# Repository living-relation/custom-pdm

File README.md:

# custom-pdm

Personal 12 V power distribution module (PDM) for car accessories: 24 outputs (16 x 7.5 A, 4 x 15 A, 4 x about 31 A on copper offset risers through the lid; one 7.5 A output, A2 OUT2, powers the internal fans, so 23 are for the car) and 24 on/off + 3 analog inputs over three boards, controlled over CAN by a Link G4X ECU.

Based on [corygrant/dingoPDM](https://github.com/corygrant/dingoPDM) (MIT). Personal project, not for sale.

Firmware: which file goes on which board, how to flash it over USB-C, how to check the version and when to update: [docs/firmware-flashing.md](docs/firmware-flashing.md).

Progress and open items: live state lives in this repo ([STATE.md](STATE.md), [BACKLOG.md](BACKLOG.md), `archives/`; see the role table in [AGENTS.md](AGENTS.md)).

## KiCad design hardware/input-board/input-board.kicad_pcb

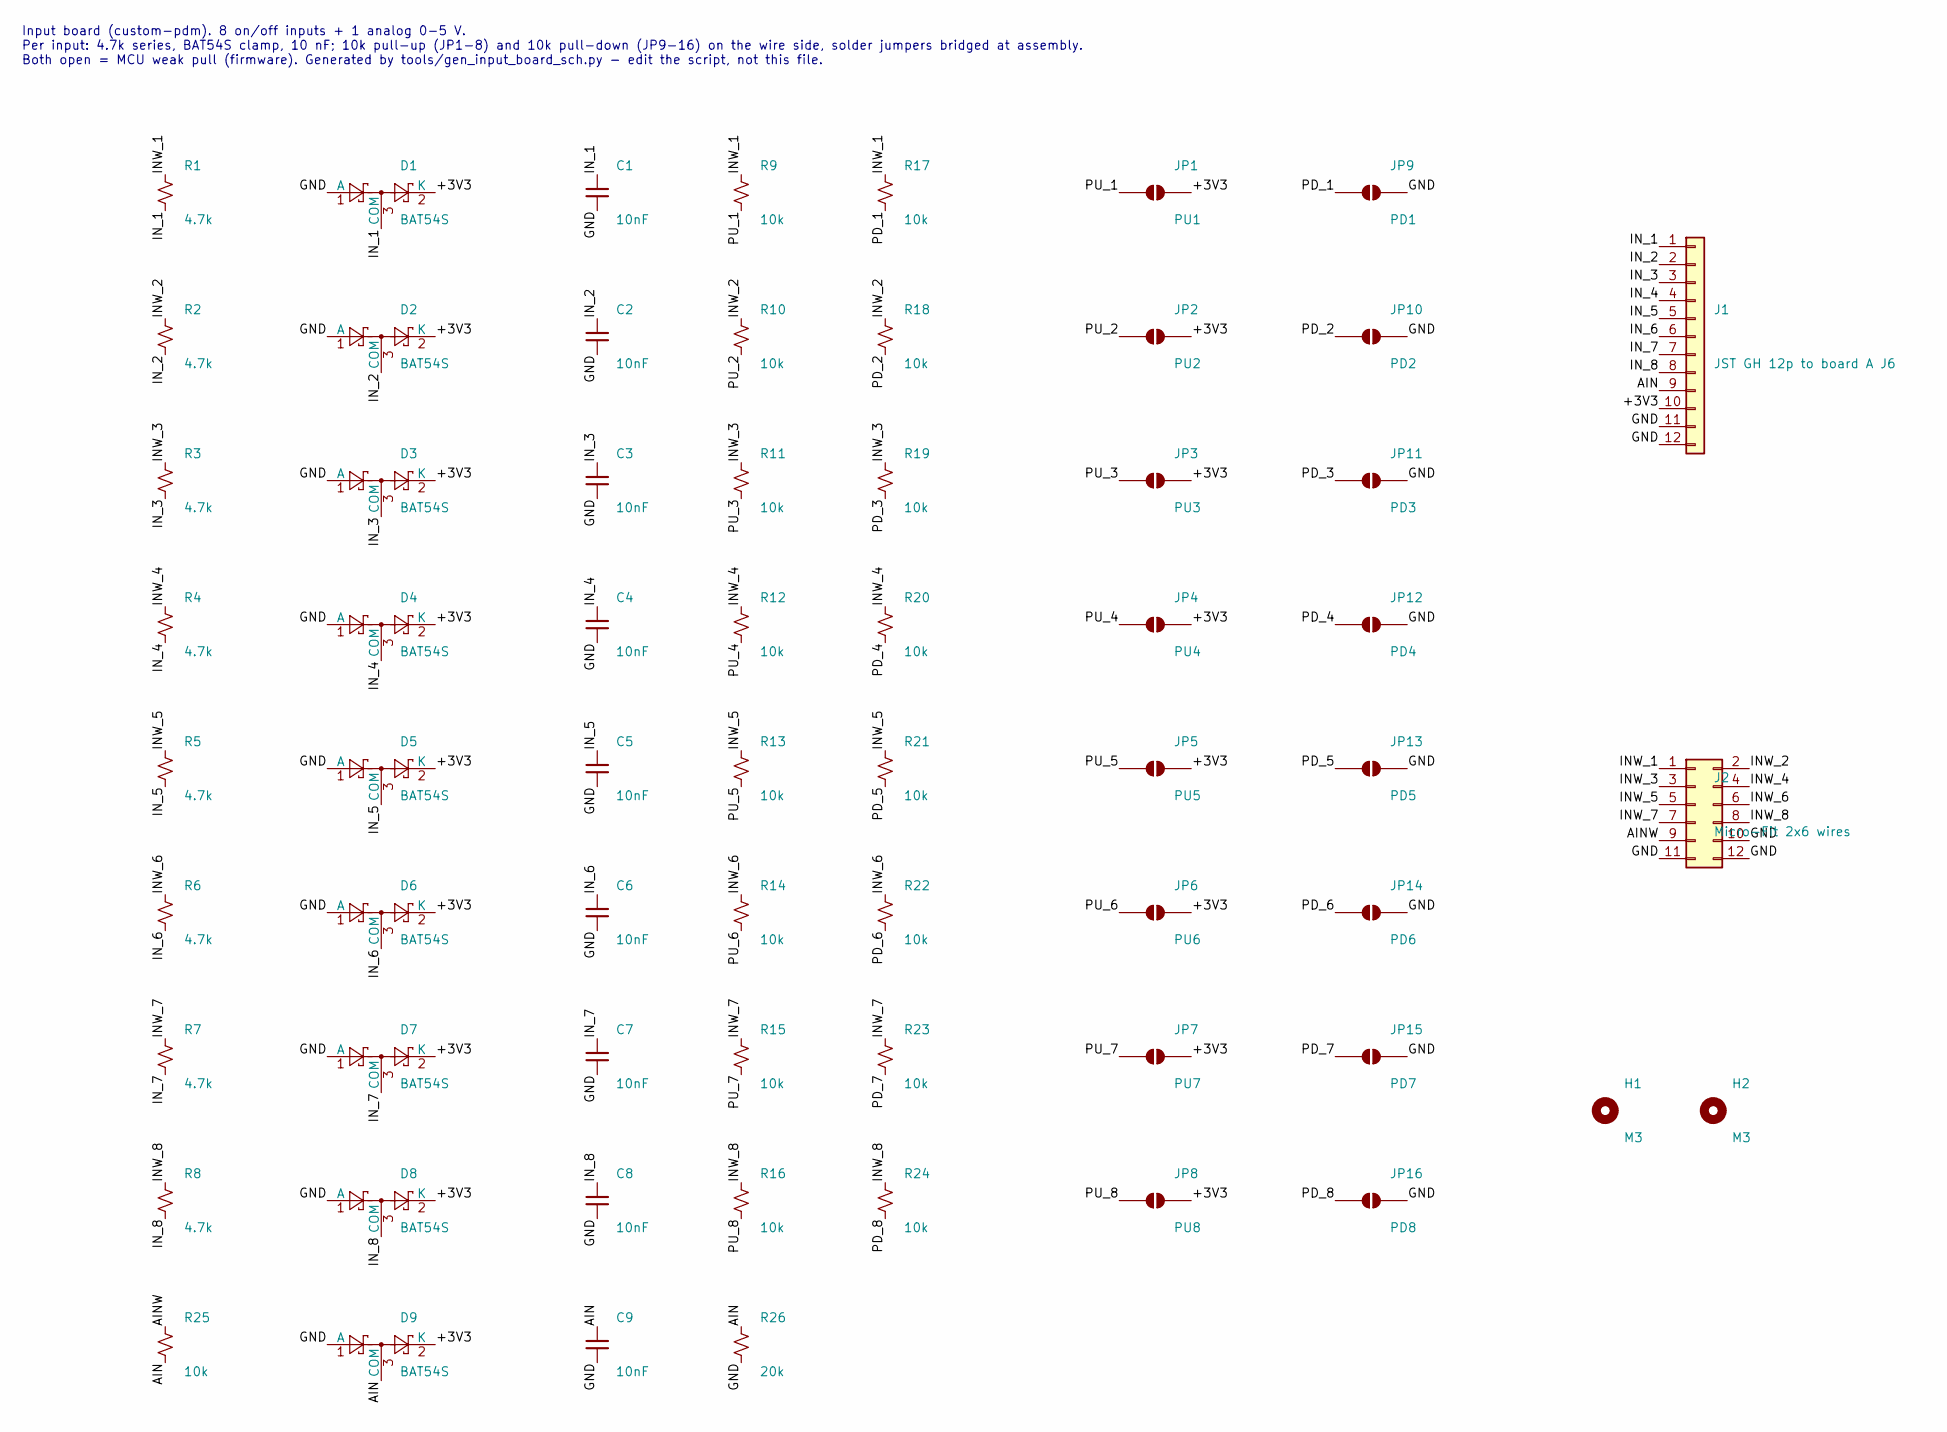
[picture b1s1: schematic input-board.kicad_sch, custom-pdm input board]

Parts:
C1, C2, C3, C4, C5, C6, C7, C8, C9: 10nF; C_0603_1608Metric; MPN 0603B103K500NT; LCSC C57112
D1, D2, D3, D4, D5, D6, D7, D8, D9: BAT54S; SOT-23; MPN BAT54S,215; LCSC C47546
H1, H2: M3; MountingHole_3.2mm_M3
J1: JST GH 12p to board A J6; JST_GH_SM12B-GHS-TB_1x12-1MP_P1.25mm_Horizontal; MPN SM12B-GHS-TB(LF)(SN); LCSC C265421
J2: Micro-Fit 2x6 wires; Molex_Micro-Fit_3.0_43045-1200_2x06_P3.00mm_Horizontal; MPN 0430451200; LCSC C277636
JP1: PU1; SolderJumper-2_P1.3mm_Open_RoundedPad1.0x1.5mm
JP2: PU2; SolderJumper-2_P1.3mm_Open_RoundedPad1.0x1.5mm
JP3: PU3; SolderJumper-2_P1.3mm_Open_RoundedPad1.0x1.5mm
JP4: PU4; SolderJumper-2_P1.3mm_Open_RoundedPad1.0x1.5mm
JP5: PU5; SolderJumper-2_P1.3mm_Open_RoundedPad1.0x1.5mm
JP6: PU6; SolderJumper-2_P1.3mm_Open_RoundedPad1.0x1.5mm
JP7: PU7; SolderJumper-2_P1.3mm_Open_RoundedPad1.0x1.5mm
JP8: PU8; SolderJumper-2_P1.3mm_Open_RoundedPad1.0x1.5mm
JP9: PD1; SolderJumper-2_P1.3mm_Open_RoundedPad1.0x1.5mm
JP10: PD2; SolderJumper-2_P1.3mm_Open_RoundedPad1.0x1.5mm
JP11: PD3; SolderJumper-2_P1.3mm_Open_RoundedPad1.0x1.5mm
JP12: PD4; SolderJumper-2_P1.3mm_Open_RoundedPad1.0x1.5mm
JP13: PD5; SolderJumper-2_P1.3mm_Open_RoundedPad1.0x1.5mm
JP14: PD6; SolderJumper-2_P1.3mm_Open_RoundedPad1.0x1.5mm
JP15: PD7; SolderJumper-2_P1.3mm_Open_RoundedPad1.0x1.5mm
JP16: PD8; SolderJumper-2_P1.3mm_Open_RoundedPad1.0x1.5mm
R1, R2, R3, R4, R5, R6, R7, R8: 4.7k; R_0603_1608Metric; MPN 0603WAF4701T5E; LCSC C23162
R9, R10, R11, R12, R13, R14, R15, R16, R17, R18, R19, R20, R21, R22, R23, R24, R25: 10k; R_0603_1608Metric; MPN 0603WAF1002T5E; LCSC C25804
R26: 20k; R_0603_1608Metric; MPN 0603WAF2002T5E; LCSC C4184

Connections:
/+3V3: D1.2 (K), D2.2 (K), D3.2 (K), D4.2 (K), D5.2 (K), D6.2 (K), D7.2 (K), D8.2 (K), D9.2 (K), J1.10, JP1.2 (B), JP2.2 (B), JP3.2 (B), JP4.2 (B), JP5.2 (B), JP6.2 (B), JP7.2 (B), JP8.2 (B)
/AIN: C9.1, D9.3 (COM), J1.9, R25.2, R26.1
/AINW: J2.9, R25.1
/GND: C1.2, C2.2, C3.2, C4.2, C5.2, C6.2, C7.2, C8.2, C9.2, D1.1 (A), D2.1 (A), D3.1 (A), D4.1 (A), D5.1 (A), D6.1 (A), D7.1 (A), D8.1 (A), D9.1 (A), J1.11, J1.12, J2.10, J2.11, J2.12, JP9.2 (B), JP10.2 (B), JP11.2 (B), JP12.2 (B), JP13.2 (B), JP14.2 (B), JP15.2 (B), JP16.2 (B), R26.2
/INW_1: J2.1, R1.1, R9.1, R17.1
/INW_2: J2.2, R2.1, R10.1, R18.1
/INW_3: J2.3, R3.1, R11.1, R19.1
/INW_4: J2.4, R4.1, R12.1, R20.1
/INW_5: J2.5, R5.1, R13.1, R21.1
/INW_6: J2.6, R6.1, R14.1, R22.1
/INW_7: J2.7, R7.1, R15.1, R23.1
/INW_8: J2.8, R8.1, R16.1, R24.1
/IN_1: C1.1, D1.3 (COM), J1.1, R1.2
/IN_2: C2.1, D2.3 (COM), J1.2, R2.2
/IN_3: C3.1, D3.3 (COM), J1.3, R3.2
/IN_4: C4.1, D4.3 (COM), J1.4, R4.2
/IN_5: C5.1, D5.3 (COM), J1.5, R5.2
/IN_6: C6.1, D6.3 (COM), J1.6, R6.2
/IN_7: C7.1, D7.3 (COM), J1.7, R7.2
/IN_8: C8.1, D8.3 (COM), J1.8, R8.2
/PD_1: JP9.1 (A), R17.2
/PD_2: JP10.1 (A), R18.2
/PD_3: JP11.1 (A), R19.2
/PD_4: JP12.1 (A), R20.2
/PD_5: JP13.1 (A), R21.2
/PD_6: JP14.1 (A), R22.2
/PD_7: JP15.1 (A), R23.2
/PD_8: JP16.1 (A), R24.2
/PU_1: JP1.1 (A), R9.2
/PU_2: JP2.1 (A), R10.2
/PU_3: JP3.1 (A), R11.2
/PU_4: JP4.1 (A), R12.2
/PU_5: JP5.1 (A), R13.2
/PU_6: JP6.1 (A), R14.2
/PU_7: JP7.1 (A), R15.2
/PU_8: JP8.1 (A), R16.2

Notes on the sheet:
Input board (custom-pdm). 8 on/off inputs + 1 analog 0-5 V. Per input: 4.7k series, BAT54S clamp, 10 nF; 10k pull-up (JP1-8) and 10k pull-down (JP9-16) on the wire side, solder jumpers bridged at assembly. Both open = MCU weak pull (firmware). Generated by tools/gen_input_board_sch.py - edit the sc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

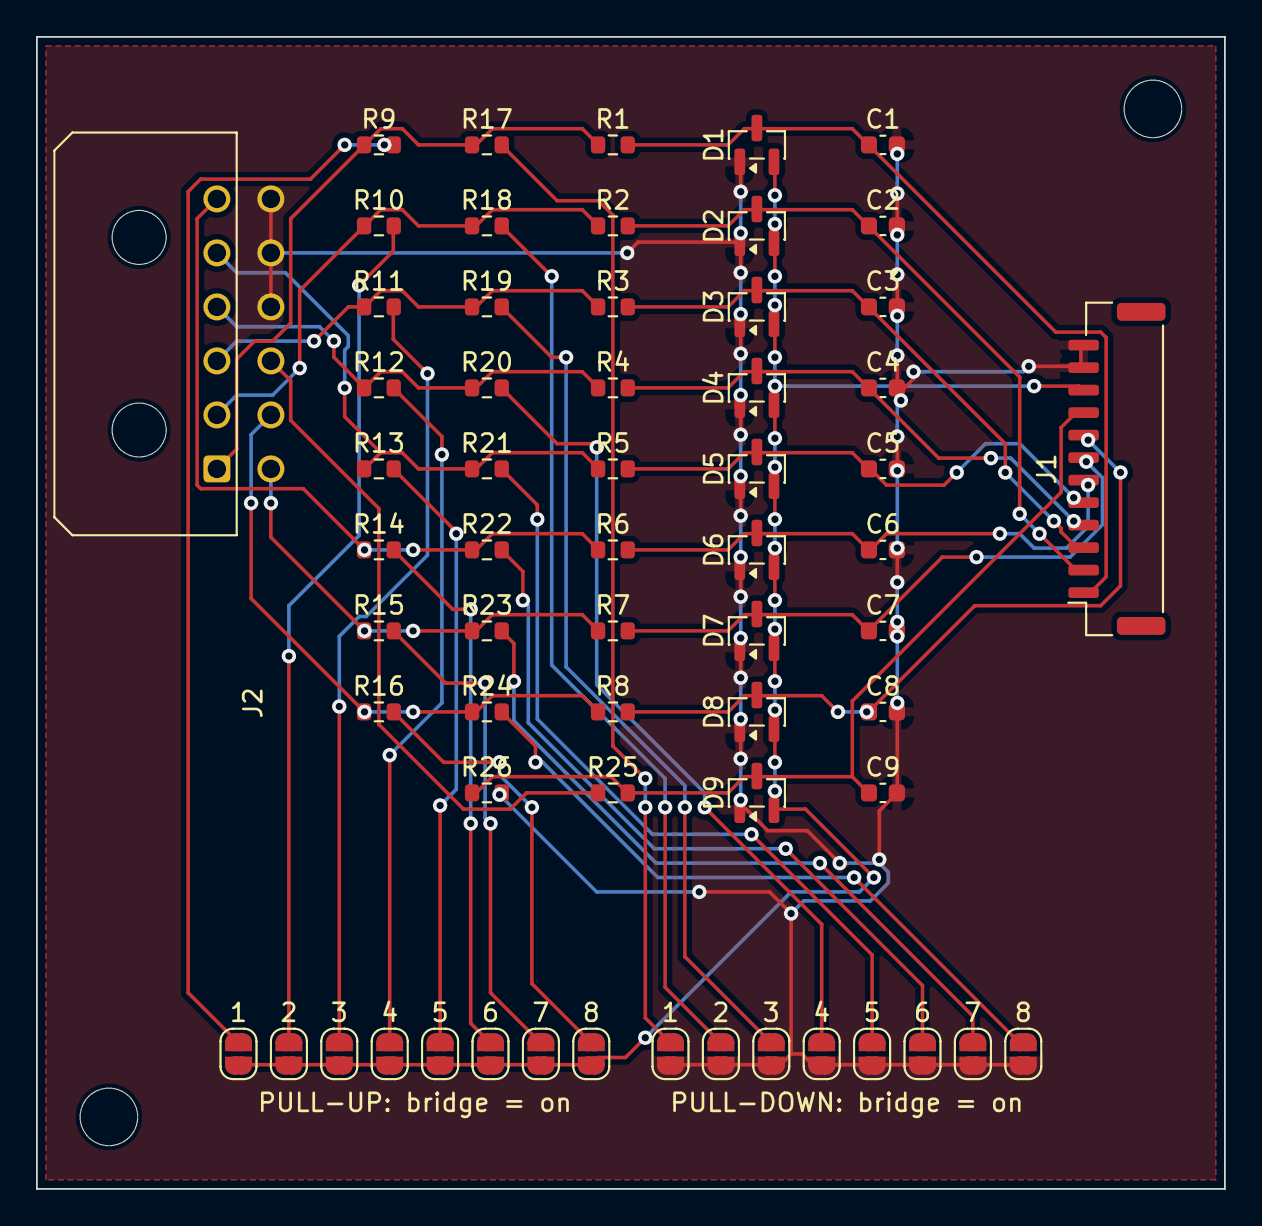
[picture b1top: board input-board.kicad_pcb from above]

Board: 2 copper layers, 66.0 x 64.0 mm, 64 parts (0 on the bottom side), 36 nets.

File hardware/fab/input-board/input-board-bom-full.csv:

Qty,Designator,Value,Footprint,Manufacturer,MPN,LCSC,Digi-Key,Approved alternates,Fitted by
9,"C1,C2,C3,C4,C5,C6,C7,C8,C9",10nF,C_0603_1608Metric,FH (Guangdong Fenghua),0603B103K500NT,C57112,311-1085-1-ND,YAGEO CC0603KRX7R9BB103 (DK 311-1085-1-ND),JLCPCB SMT
9,"D1,D2,D3,D4,D5,D6,D7,D8,D9",BAT54S,SOT-23,Nexperia,"BAT54S,215",C47546,BAT54SLT1GOSCT-ND,onsemi BAT54SLT1G (DK BAT54SLT1GOSCT-ND),JLCPCB SMT
1,J1,JST GH 12p to board A J6,JST_GH_SM12B-GHS-TB_1x12-1MP_P1.25mm_Horizontal,JST,SM12B-GHS-TB(LF)(SN),C265421,455-1574-1-ND,,JLCPCB SMT
1,J2,Micro-Fit 2x6 wires,Molex_Micro-Fit_3.0_43045-1200_2x06_P3.00mm_Horizontal,Molex,0430451200,C277636,WM1818-ND,,JLCPCB THT
8,"R1,R2,R3,R4,R5,R6,R7,R8",4.7k,R_0603_1608Metric,UNI-ROYAL,0603WAF4701T5E,C23162,311-4.70KHRCT-ND,YAGEO RC0603FR-074K7L (DK 311-4.70KHRCT-ND),JLCPCB SMT
17,"R9,R10,R11,R12,R13,R14,R15,R16,R17,R18,R19,R20,R21,R22,R23,R24,R25",10k,R_0603_1608Metric,UNI-ROYAL,0603WAF1002T5E,C25804,311-10.0KHRCT-ND,YAGEO RC0603FR-0710KL (DK 311-10.0KHRCT-ND),JLCPCB SMT
1,R26,20k,R_0603_1608Metric,UNI-ROYAL,0603WAF2002T5E,C4184,311-20.0KHRCT-ND,YAGEO RC0603FR-0720KL (DK 311-20.0KHRCT-ND),JLCPCB SMT

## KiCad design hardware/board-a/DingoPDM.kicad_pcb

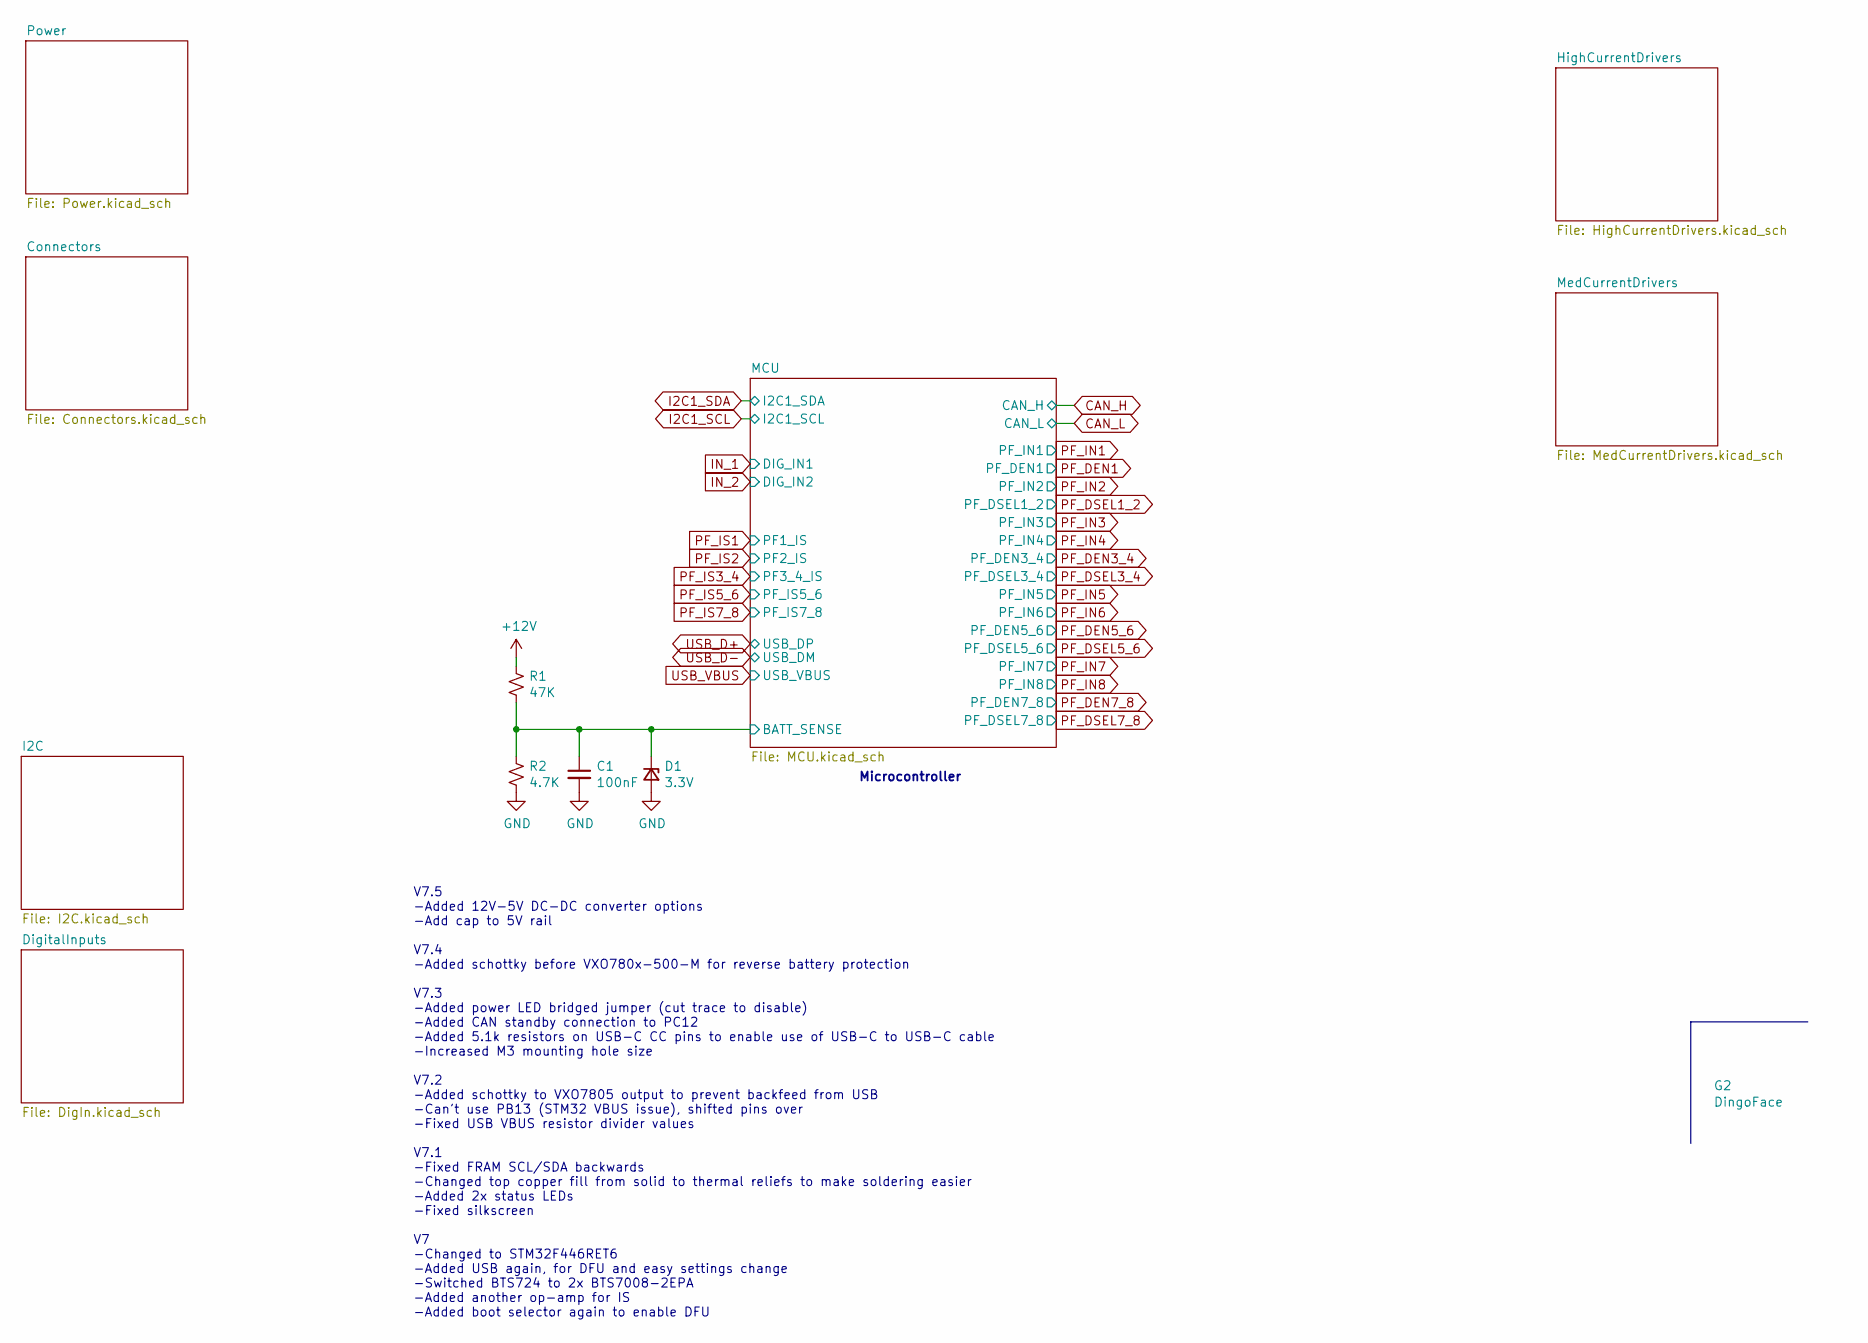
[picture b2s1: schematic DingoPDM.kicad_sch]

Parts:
C1: 100nF; C_0805_2012Metric; MPN CC0805KRX7R9BB104; Digi-Key_PN 478-1395-1-ND
D1: 3.3V; D_SOD-323_HandSoldering; MPN PDZ3.3B,115; Digi-Key_PN 1727-5150-1-ND
G2: DingoFace; DingoFaceNoFill
R1: 47K; R_0805_2012Metric; MPN RT0805DRD0747KL; Digi-Key_PN 311-47.0KCRCT-ND
R2: 4.7K; R_0805_2012Metric; MPN 0805W8F4701T5E; Digi-Key_PN 311-4.70KCRCT-ND

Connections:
+12V: R1.1; also elsewhere on the board
/MCU/BATT_SENSE: C1.1, D1.1 (K), R1.2, R2.1; also elsewhere on the board
GND: C1.2, D1.2 (A), R2.2; also elsewhere on the board

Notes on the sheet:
Microcontroller
V7.5 -Added 12V-5V DC-DC converter options -Add cap to 5V rail V7.4 -Added schottky before VXO780x-500-M for reverse battery protection V7.3 -Added power LED bridged jumper (cut trace to disable) -Added CAN standby connection to PC12 -Added 5.1k resistors on USB-C CC pins to enable use of USB-C to 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

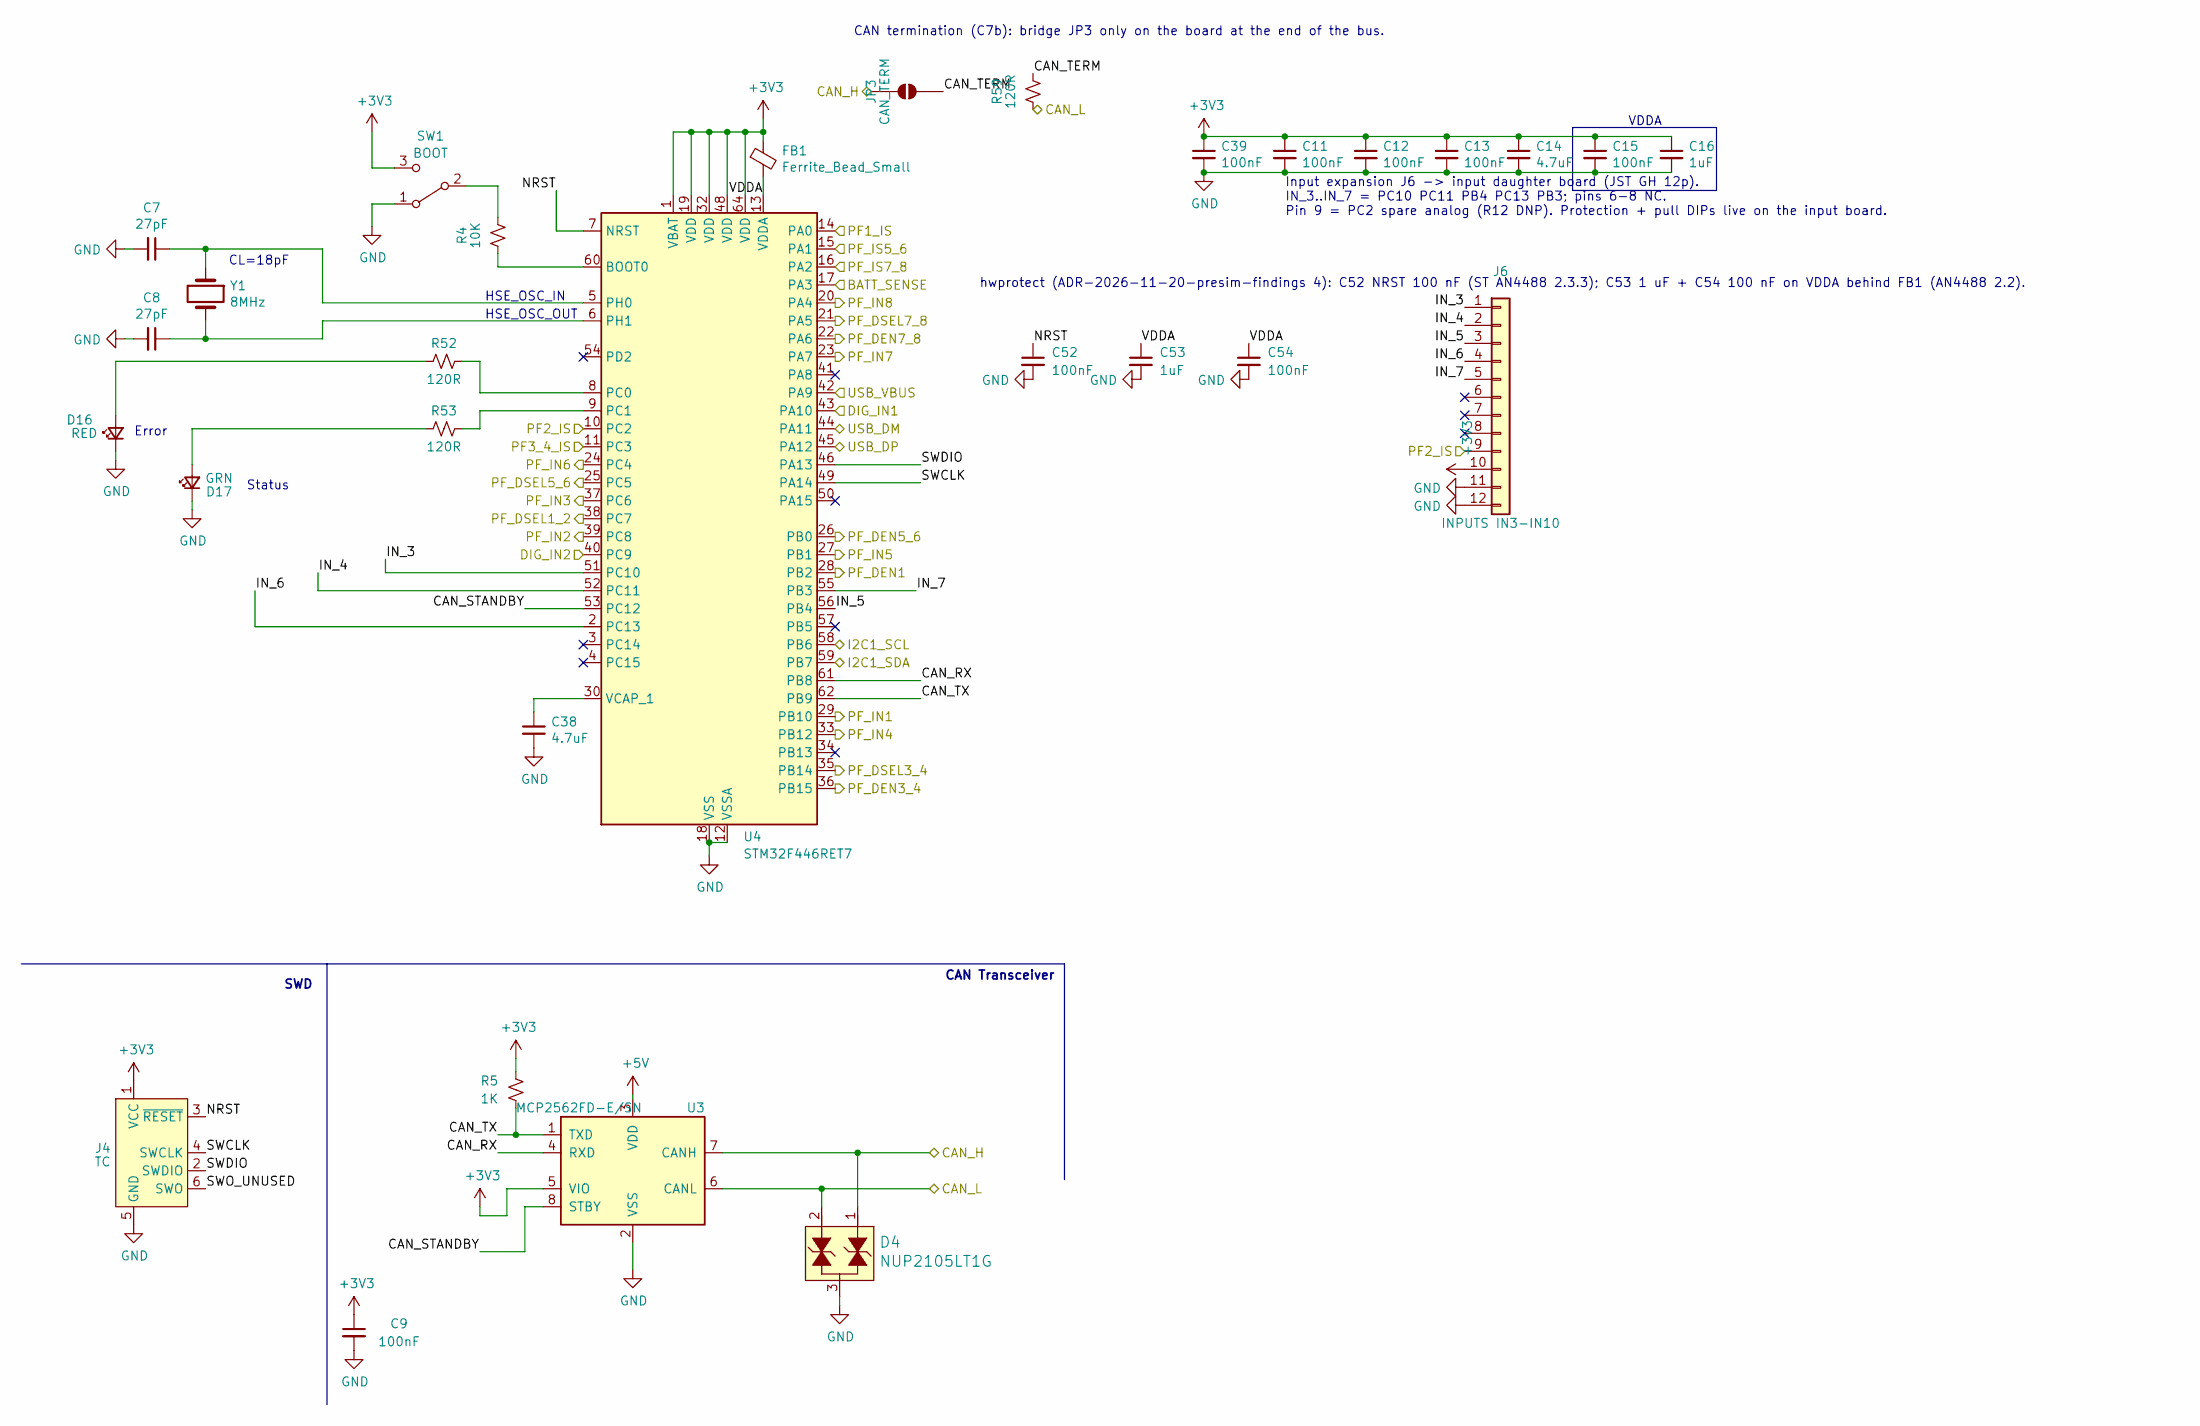
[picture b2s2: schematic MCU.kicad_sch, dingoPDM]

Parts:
C7, C8: 27pF; C_0805_2012Metric; MPN 0805CG270J500NT; Digi-Key_PN 478-10518-1-ND
C9, C11, C12, C13, C15, C39: 100nF; C_0805_2012Metric; MPN CC0805KRX7R9BB104; Digi-Key_PN 478-1395-1-ND
C14, C38: 4.7uF; C_0805_2012Metric; MPN CL21B475KAFNNNE; LCSC C98195
C16: 1uF; C_0805_2012Metric; MPN CL21B105KBFNNNE; Digi-Key_PN 311-1365-1-ND
C52, C54: 100nF; C_0402_1005Metric; MPN CL05B104KO5NNNC; LCSC C1525
C53: 1uF; C_0402_1005Metric; MPN TCC0402X7R105K100AT; LCSC C47325373
D4: NUP2105LT1G; SOT-23-3; MPN NUP2105LT1G; Digi-Key_PN NUP2105LT1GOSCT-ND
D16: RED; LED_0805_2012Metric; MPN LS R976-NR-1-0-20-R18; Digi-Key_PN 475-1278-1-ND
D17: GRN; LED_0805_2012Metric; MPN LG R971-KN-1-0-20-R18; Digi-Key_PN 475-1410-1-ND
FB1: Ferrite_Bead_Small; R_0805_2012Metric; MPN BLM21PG221SN1D; Digi-Key_PN 490-1054-1-ND
J4: TC; Tag-Connect_TC2030-IDC-NL_2x03_P1.27mm_Vertical
J6: INPUTS IN3-IN10; JST_GH_SM12B-GHS-TB_1x12-1MP_P1.25mm_Horizontal; MPN SM12B-GHS-TB(LF)(SN); LCSC C265421
JP3: CAN_TERM; SolderJumper-2_P1.3mm_Open_RoundedPad1.0x1.5mm
R4: 10K; R_0805_2012Metric; MPN 0805W8F1002T5E; Digi-Key_PN 311-10.0KCRDKR-ND
R5: 1K; R_0805_2012Metric; MPN 0805W8F1001T5E; Digi-Key_PN 311-1.0KARCT-ND
R52, R53, R59: 120R; R_0805_2012Metric; MPN 0805W8F1200T5E; Digi-Key_PN 311-120CRCT-ND
SW1: BOOT; CJS-1200TB; MPN CJS-1200TB1; Digi-Key_PN 563-CJS-1200TB1CT-ND
U3: MCP2562FD-E/SN; SOIC-8_3.9x4.9mm_P1.27mm; MPN MCP2562FD-E/SN; Digi-Key_PN MCP2562FD-E/SN-ND
U4: STM32F446RET7; LQFP-64_10x10mm_P0.5mm; MPN STM32F446RET7; Digi-Key_PN 497-16775-ND
Y1: 8MHz; Crystal_SMD_5032-2Pin_5.0x3.2mm_HandSoldering; MPN ECS-80-18-30Q-CES-TR; Digi-Key_PN 50-ECS-80-18-30Q-CES-TRCT-ND

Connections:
+3V3: C9.1, C11.1, C12.1, C13.1, C14.1, C15.1, C16.1, C39.1, FB1.1, J4.1 (VCC), J6.10, R5.2, SW1.3 (C), U3.5 (Vref), U4.1 (VBAT), U4.19 (VDD), U4.32 (VDD), U4.48 (VDD), U4.64 (VDD); also elsewhere on the board
+5V: U3.3 (VDD); also elsewhere on the board
/MCU/BATT_SENSE: U4.17 (PA3); also elsewhere on the board
/MCU/CAN_RX: U3.4 (RXD), U4.61 (PB8)
/MCU/CAN_STANDBY: U3.8 (Rs), U4.53 (PC12)
/MCU/CAN_TERM: JP3.2 (B), R59.1
/MCU/CAN_TX: R5.1, U3.1 (TXD), U4.62 (PB9)
/MCU/IN_3: J6.1, U4.51 (PC10)
/MCU/IN_4: J6.2, U4.52 (PC11)
/MCU/IN_5: J6.3, U4.56 (PB4)
/MCU/IN_6: J6.4, U4.2 (PC13)
/MCU/IN_7: J6.5, U4.55 (PB3)
/MCU/NRST: C52.1, J4.3 (~RESET), U4.7 (NRST)
/MCU/SWCLK: J4.4 (SWCLK), U4.49 (PA14)
/MCU/SWDIO: J4.2 (SWDIO), U4.46 (PA13)
/MCU/SWO_UNUSED: J4.6 (SWO)
/MCU/VDDA: C53.1, C54.1, FB1.2, U4.13 (VDDA)
CAN_H: D4.1, JP3.1 (A), U3.7 (CANH); also elsewhere on the board
CAN_L: D4.2, R59.2, U3.6 (CANL); also elsewhere on the board
GND: C7.2, C8.2, C9.2, C11.2, C12.2, C13.2, C14.2, C15.2, C16.2, C38.2, C39.2, C52.2, C53.2, C54.2, D4.3, D16.1 (K), D17.1 (K), J4.5 (GND), J6.11, J6.12, SW1.1 (A), U3.2 (VSS), U4.12 (VSSA), U4.18 (VSS), U4.31 (VSS), U4.47 (VSS), U4.63 (VSS); also elsewhere on the board
I2C1_SCL: U4.58 (PB6); also elsewhere on the board
I2C1_SDA: U4.59 (PB7); also elsewhere on the board
IN_1: U4.43 (PA10); also elsewhere on the board
IN_2: U4.40 (PC9); also elsewhere on the board
unnamed: D16.2 (A), R52.2
unnamed: D17.2 (A), R53.2
unnamed: R4.1, SW1.2 (B)
unnamed: R4.2, U4.60 (BOOT0)
unnamed: R52.1, U4.8 (PC0)
unnamed: R53.1, U4.9 (PC1)
unnamed: C7.1, U4.5 (PH0), Y1.1
unnamed: C8.1, U4.6 (PH1), Y1.2
unnamed: C38.1, U4.30 (VCAP_1)
PF_DEN1: U4.28 (PB2); also elsewhere on the board
PF_DEN3_4: U4.36 (PB15); also elsewhere on the board
PF_DEN5_6: U4.26 (PB0); also elsewhere on the board
PF_DEN7_8: U4.22 (PA6); also elsewhere on the board
PF_DSEL1_2: U4.38 (PC7); also elsewhere on the board
PF_DSEL3_4: U4.35 (PB14); also elsewhere on the board
PF_DSEL5_6: U4.25 (PC5); also elsewhere on the board
PF_DSEL7_8: U4.21 (PA5); also elsewhere on the board
PF_IN1: U4.29 (PB10); also elsewhere on the board
PF_IN2: U4.39 (PC8); also elsewhere on the board
PF_IN3: U4.37 (PC6); also elsewhere on the board
PF_IN4: U4.33 (PB12); also elsewhere on the board
PF_IN5: U4.27 (PB1); also elsewhere on the board
PF_IN6: U4.24 (PC4); also elsewhere on the board
PF_IN7: U4.23 (PA7); also elsewhere on the board
PF_IN8: U4.20 (PA4); also elsewhere on the board
PF_IS1: U4.14 (PA0); also elsewhere on the board
PF_IS2: J6.9, U4.10 (PC2); also elsewhere on the board
PF_IS3_4: U4.11 (PC3); also elsewhere on the board
PF_IS5_6: U4.15 (PA1); also elsewhere on the board
PF_IS7_8: U4.16 (PA2); also elsewhere on the board
USB_D+: U4.45 (PA12); also elsewhere on the board
USB_D-: U4.44 (PA11); also elsewhere on the board
USB_VBUS: U4.42 (PA9); also elsewhere on the board

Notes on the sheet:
SWD
Error
CAN Transceiver
HSE_OSC_IN
CL=18pF
HSE_OSC_OUT
VDDA
Status
Input expansion J6 -> input daughter board (JST GH 12p). IN_3..IN_7 = PC10 PC11 PB4 PC13 PB3; pins 6-8 NC. Pin 9 = PC2 spare analog (R12 DNP). Protection + pull DIPs live on the input board.
CAN termination (C7b): bridge JP3 only on the board at the end of the bus.
hwprotect (ADR-2026-11-20-presim-findings 4): C52 NRST 100 nF (ST AN4488 2.3.3); C53 1 uF + C54 100 nF on VDDA behind FB1 (AN4488 2.2).

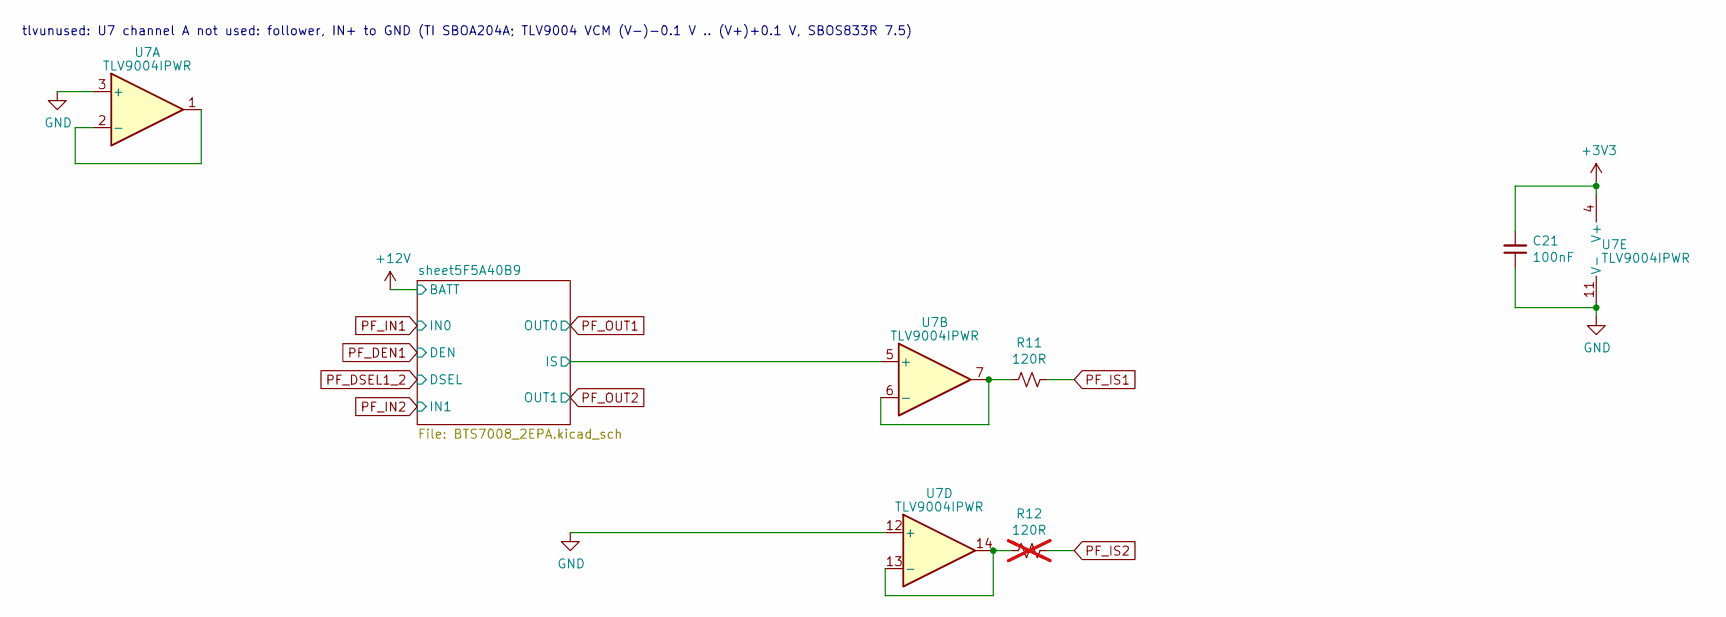
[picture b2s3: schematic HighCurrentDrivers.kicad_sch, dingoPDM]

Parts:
C21: 100nF; C_0805_2012Metric; MPN CC0805KRX7R9BB104; Digi-Key_PN 478-1395-1-ND
R11: 120R; R_0805_2012Metric; MPN 0805W8F1200T5E; Digi-Key_PN 311-120CRCT-ND
R12: 120R; R_0805_2012Metric; MPN 0805W8F1200T5E; Digi-Key_PN 311-120CRCT-ND; not fitted
U7: TLV9004IPWR; TSSOP-14_4.4x5mm_P0.65mm; MPN TLV9004IPWR; Digi-Key_PN 296-51827-1-ND

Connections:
+3V3: C21.2, U7.4 (V+); also elsewhere on the board
/HighCurrentDrivers/sheet5F5A40B9/IS: U7.5 (+); also elsewhere on the board
GND: C21.1, U7.3 (+), U7.11 (V-), U7.12 (+); also elsewhere on the board
unnamed: U7.1, U7.2 (-)
unnamed: R11.2, U7.6 (-), U7.7
unnamed: R12.2, U7.13 (-), U7.14
PF_IS1: R11.1; also elsewhere on the board
PF_IS2: R12.1; also elsewhere on the board

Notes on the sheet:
tlvunused: U7 channel A not used: follower, IN+ to GND (TI SBOA204A; TLV9004 VCM (V-)-0.1 V .. (V+)+0.1 V, SBOS833R 7.5)

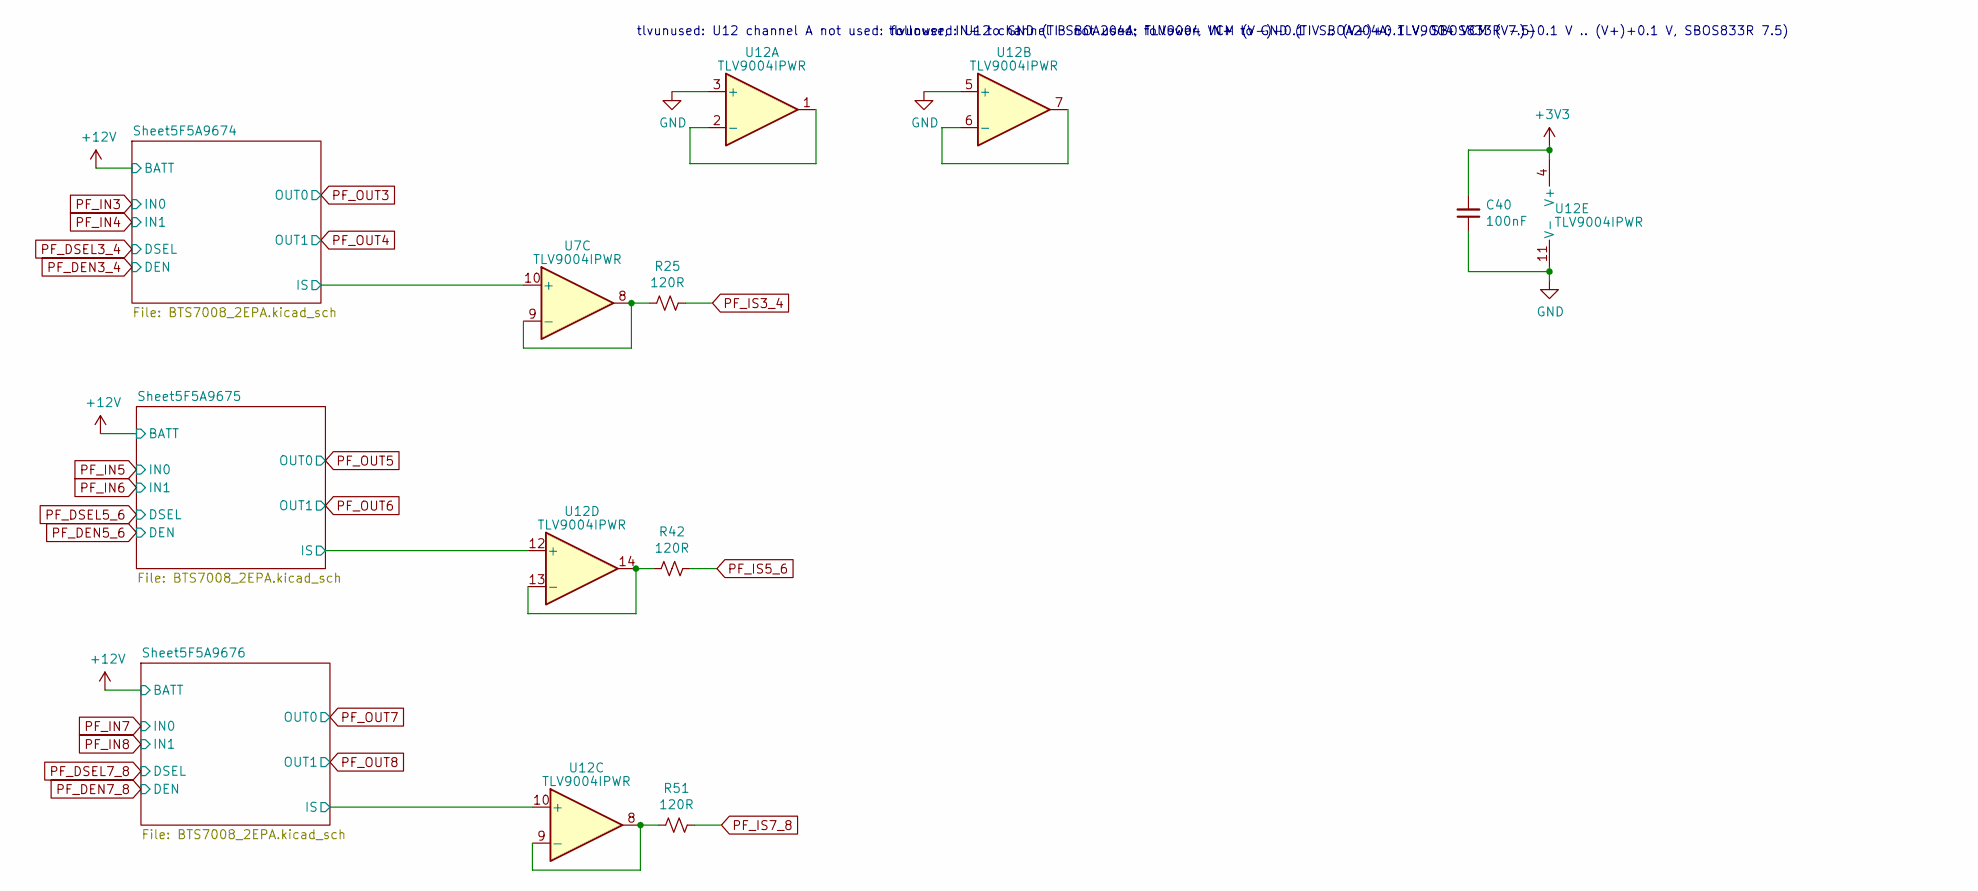
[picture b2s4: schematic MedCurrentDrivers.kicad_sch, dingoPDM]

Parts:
C40: 100nF; C_0805_2012Metric; MPN CC0805KRX7R9BB104; Digi-Key_PN 478-1395-1-ND
R25, R42, R51: 120R; R_0805_2012Metric; MPN 0805W8F1200T5E; Digi-Key_PN 311-120CRCT-ND
U7, U12: TLV9004IPWR; TSSOP-14_4.4x5mm_P0.65mm; MPN TLV9004IPWR; Digi-Key_PN 296-51827-1-ND

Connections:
+3V3: C40.2, U12.4 (V+); also elsewhere on the board
/MedCurrentDrivers/Sheet5F5A9674/IS: U7.10 (+); also elsewhere on the board
/MedCurrentDrivers/Sheet5F5A9675/IS: U12.12 (+); also elsewhere on the board
/MedCurrentDrivers/Sheet5F5A9676/IS: U12.10 (+); also elsewhere on the board
GND: C40.1, U12.3 (+), U12.5 (+), U12.11 (V-); also elsewhere on the board
unnamed: R25.2, U7.8, U7.9 (-)
unnamed: U12.1, U12.2 (-)
unnamed: U12.6 (-), U12.7
unnamed: R51.2, U12.8, U12.9 (-)
unnamed: R42.2, U12.13 (-), U12.14
PF_IS3_4: R25.1; also elsewhere on the board
PF_IS5_6: R42.1; also elsewhere on the board
PF_IS7_8: R51.1; also elsewhere on the board

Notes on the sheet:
tlvunused: U12 channel A not used: follower, IN+ to GND (TI SBOA204A; TLV9004 VCM (V-)-0.1 V .. (V+)+0.1 V, SBOS833R 7.5)
tlvunused: U12 channel B not used: follower, IN+ to GND (TI SBOA204A; TLV9004 VCM (V-)-0.1 V .. (V+)+0.1 V, SBOS833R 7.5)

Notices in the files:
firmware/boards/custompdm_b/board.h:
ChibiOS - Copyright (C) 2006..2023 Giovanni Di Sirio
Licensed under the Apache License, Version 2.0 (the "License");
